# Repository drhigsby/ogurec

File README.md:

# ogurec
A 12u X 3u reversible ortholinear keyborb

Left-sided PM = components away from PCB

Right-sided PM = components towards PCB

http://www.keyboard-layout-editor.com/#/gists/f1bda3a87822868599cf6e3c4340f594

Ogurec (Огурец) means 'Cucumber' in Russian. The name is a play on 'Gherkin', a 3x10 board, because the 3x12 layout supports all the letter keys of Jcuken (Russian equivalent of qwerty) unlike the 30-keyed Gherkin.

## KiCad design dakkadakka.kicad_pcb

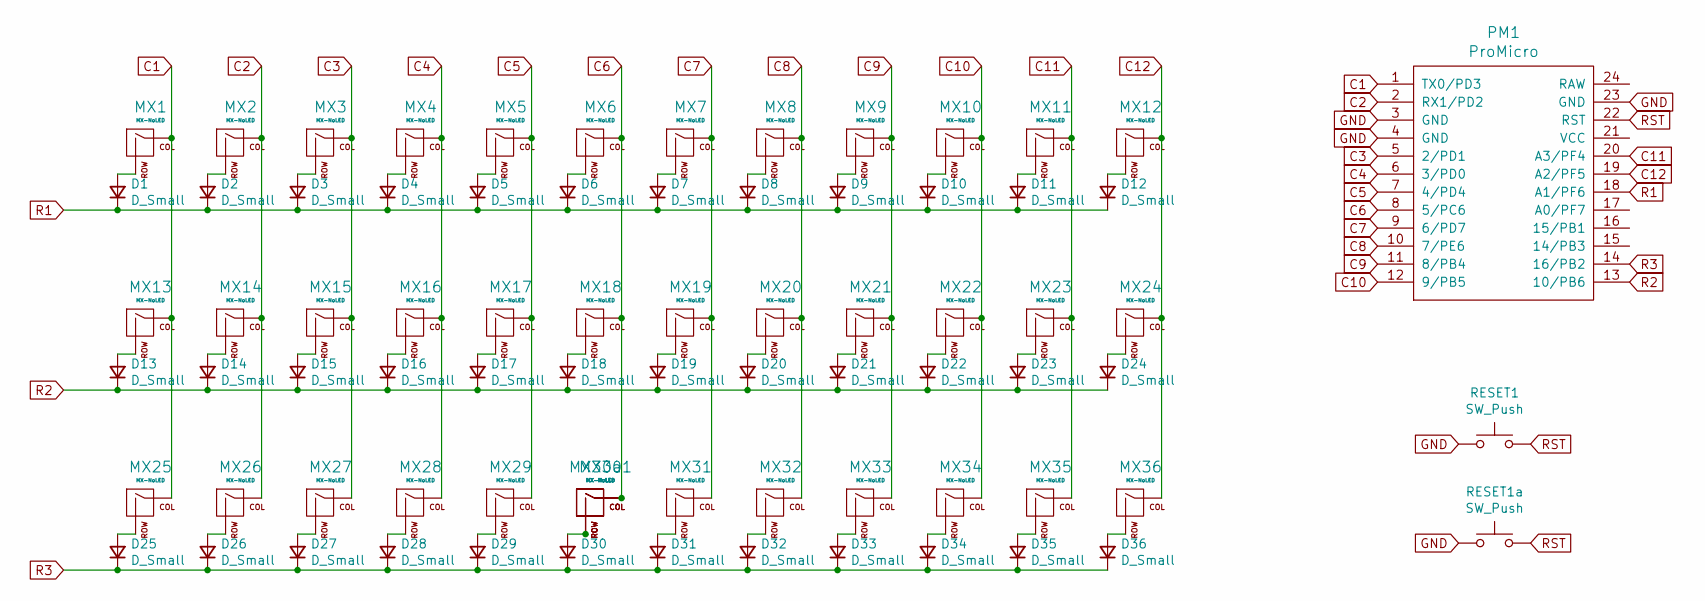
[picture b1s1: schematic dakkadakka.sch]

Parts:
D1, D2, D3, D4, D5, D6, D7, D8, D9, D10, D11, D12, D13, D14, D15, D16, D17, D18, D19, D20, D21, D22, D23, D24, D25, D26, D27, D28, D29, D30, D31, D32, D33, D34, D35, D36: D_Small; Diode-dual
MX1, MX2, MX3, MX4, MX5, MX6, MX7, MX8, MX9, MX10, MX11, MX12, MX13, MX14, MX15, MX16, MX17, MX18, MX19, MX20, MX21, MX22, MX23, MX24, MX25, MX26, MX27, MX28, MX29, MX30, MX31, MX32, MX33, MX34, MX35, MX36: MX-NoLED; MX_ONLY_1u_NOLED_REVERSIBLE
MX30a1: MX-NoLED; MXOnly-2U-NoLED-REVERSIBLE
PM1: ProMicro; ArduinoProMicro
RESET1, RESET1a: SW_Push; SW_SPST_SKQG_WithoutStem

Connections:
C1: MX1.1 (COL), MX13.1 (COL), MX25.1 (COL), PM1.1 (TX0/PD3)
C2: MX2.1 (COL), MX14.1 (COL), MX26.1 (COL), PM1.2 (RX1/PD2)
C3: MX3.1 (COL), MX15.1 (COL), MX27.1 (COL), PM1.5 (2/PD1)
C4: MX4.1 (COL), MX16.1 (COL), MX28.1 (COL), PM1.6 (3/PD0)
C5: MX5.1 (COL), MX17.1 (COL), MX29.1 (COL), PM1.7 (4/PD4)
C6: MX6.1 (COL), MX18.1 (COL), MX30.1 (COL), MX30a1.1 (COL), PM1.8 (5/PC6)
C7: MX7.1 (COL), MX19.1 (COL), MX31.1 (COL), PM1.9 (6/PD7)
C8: MX8.1 (COL), MX20.1 (COL), MX32.1 (COL), PM1.10 (7/PE6)
C9: MX9.1 (COL), MX21.1 (COL), MX33.1 (COL), PM1.11 (8/PB4)
C10: MX10.1 (COL), MX22.1 (COL), MX34.1 (COL), PM1.12 (9/PB5)
C11: MX11.1 (COL), MX23.1 (COL), MX35.1 (COL), PM1.20 (A3/PF4)
C12: MX12.1 (COL), MX24.1 (COL), MX36.1 (COL), PM1.19 (A2/PF5)
GND: PM1.3 (GND), PM1.4 (GND), PM1.23 (GND), RESET1.1, RESET1a.1; also elsewhere on the board
unnamed: D1.2 (A), MX1.2 (ROW)
unnamed: D2.2 (A), MX2.2 (ROW)
unnamed: D3.2 (A), MX3.2 (ROW)
unnamed: D4.2 (A), MX4.2 (ROW)
unnamed: D5.2 (A), MX5.2 (ROW)
unnamed: D6.2 (A), MX6.2 (ROW)
unnamed: D7.2 (A), MX7.2 (ROW)
unnamed: D8.2 (A), MX8.2 (ROW)
unnamed: D9.2 (A), MX9.2 (ROW)
unnamed: D10.2 (A), MX10.2 (ROW)
unnamed: D11.2 (A), MX11.2 (ROW)
unnamed: D12.2 (A), MX12.2 (ROW)
unnamed: D13.2 (A), MX13.2 (ROW)
unnamed: D14.2 (A), MX14.2 (ROW)
unnamed: D15.2 (A), MX15.2 (ROW)
unnamed: D16.2 (A), MX16.2 (ROW)
unnamed: D17.2 (A), MX17.2 (ROW)
unnamed: D18.2 (A), MX18.2 (ROW)
unnamed: D19.2 (A), MX19.2 (ROW)
unnamed: D20.2 (A), MX20.2 (ROW)
unnamed: D21.2 (A), MX21.2 (ROW)
unnamed: D22.2 (A), MX22.2 (ROW)
unnamed: D23.2 (A), MX23.2 (ROW)
unnamed: D24.2 (A), MX24.2 (ROW)
unnamed: D25.2 (A), MX25.2 (ROW)
unnamed: D26.2 (A), MX26.2 (ROW)
unnamed: D27.2 (A), MX27.2 (ROW)
unnamed: D28.2 (A), MX28.2 (ROW)
unnamed: D29.2 (A), MX29.2 (ROW)
unnamed: D30.2 (A), MX30.2 (ROW), MX30a1.2 (ROW)
unnamed: D31.2 (A), MX31.2 (ROW)
unnamed: D32.2 (A), MX32.2 (ROW)
unnamed: D33.2 (A), MX33.2 (ROW)
unnamed: D34.2 (A), MX34.2 (ROW)
unnamed: D35.2 (A), MX35.2 (ROW)
unnamed: D36.2 (A), MX36.2 (ROW)
R1: D1.1 (K), D2.1 (K), D3.1 (K), D4.1 (K), D5.1 (K), D6.1 (K), D7.1 (K), D8.1 (K), D9.1 (K), D10.1 (K), D11.1 (K), D12.1 (K), PM1.18 (A1/PF6)
R2: D13.1 (K), D14.1 (K), D15.1 (K), D16.1 (K), D17.1 (K), D18.1 (K), D19.1 (K), D20.1 (K), D21.1 (K), D22.1 (K), D23.1 (K), D24.1 (K), PM1.13 (10/PB6)
R3: D25.1 (K), D26.1 (K), D27.1 (K), D28.1 (K), D29.1 (K), D30.1 (K), D31.1 (K), D32.1 (K), D33.1 (K), D34.1 (K), D35.1 (K), D36.1 (K), PM1.14 (16/PB2)
RST: PM1.22 (RST), RESET1.2, RESET1a.2; also elsewhere on the board

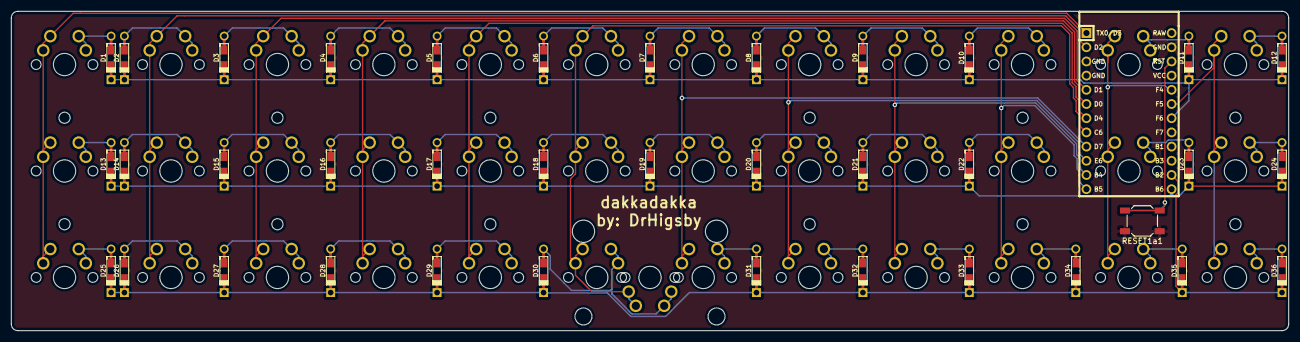
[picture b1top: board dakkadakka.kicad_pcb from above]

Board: 2 copper layers, 228.6 x 57.2 mm, 76 parts (1 on the bottom side), 53 nets.

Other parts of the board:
RESET1a1: SW_Push; SW_SPST_SKQG_WithoutStem

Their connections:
GND: RESET1a1.1; also elsewhere on the board
RST: RESET1a1.2; also elsewhere on the board

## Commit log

2021-06-01 Reversible PCB update
    Reversible PCB update
2021-06-01 updated pcb render
    updated pcb render
2021-06-01 ogurec name change
    ogurec name change
2021-06-21 removing individual pcb gerbers (they are in a zip)
2021-06-21 adding 3dp files (made by Glow)
2021-06-21 added 3dp case readme
2021-06-21 removed unnecessary text
2021-06-21 added new description from Dack
2021-06-21 fixing readme
2021-07-07 Fixing sidedness description
